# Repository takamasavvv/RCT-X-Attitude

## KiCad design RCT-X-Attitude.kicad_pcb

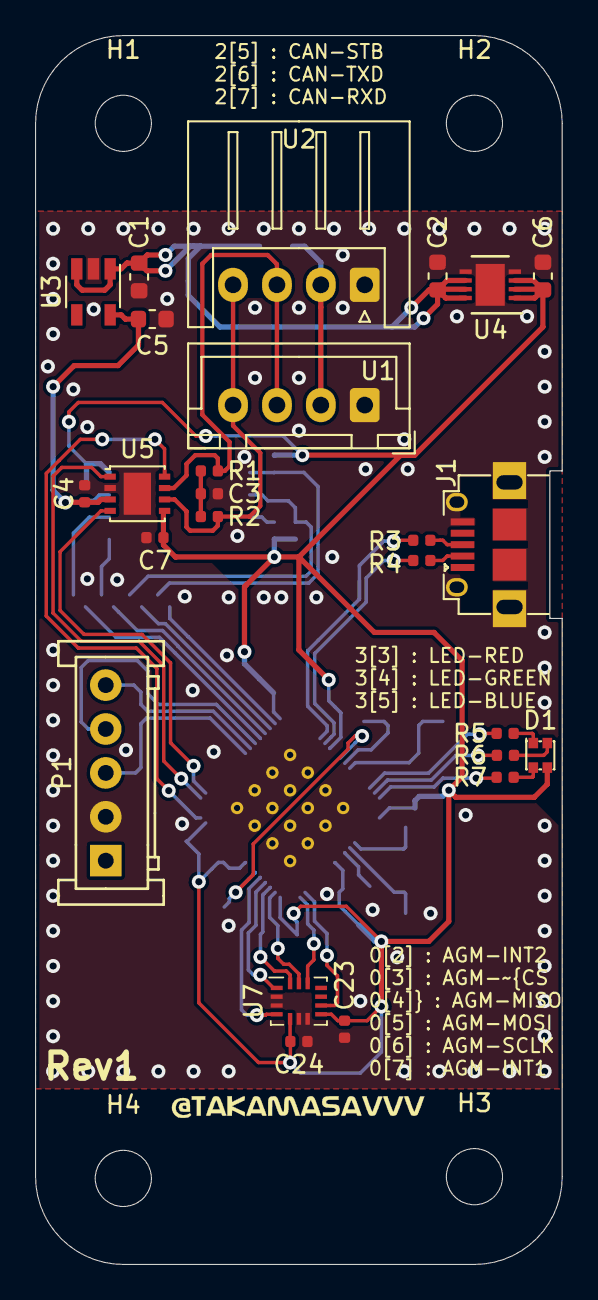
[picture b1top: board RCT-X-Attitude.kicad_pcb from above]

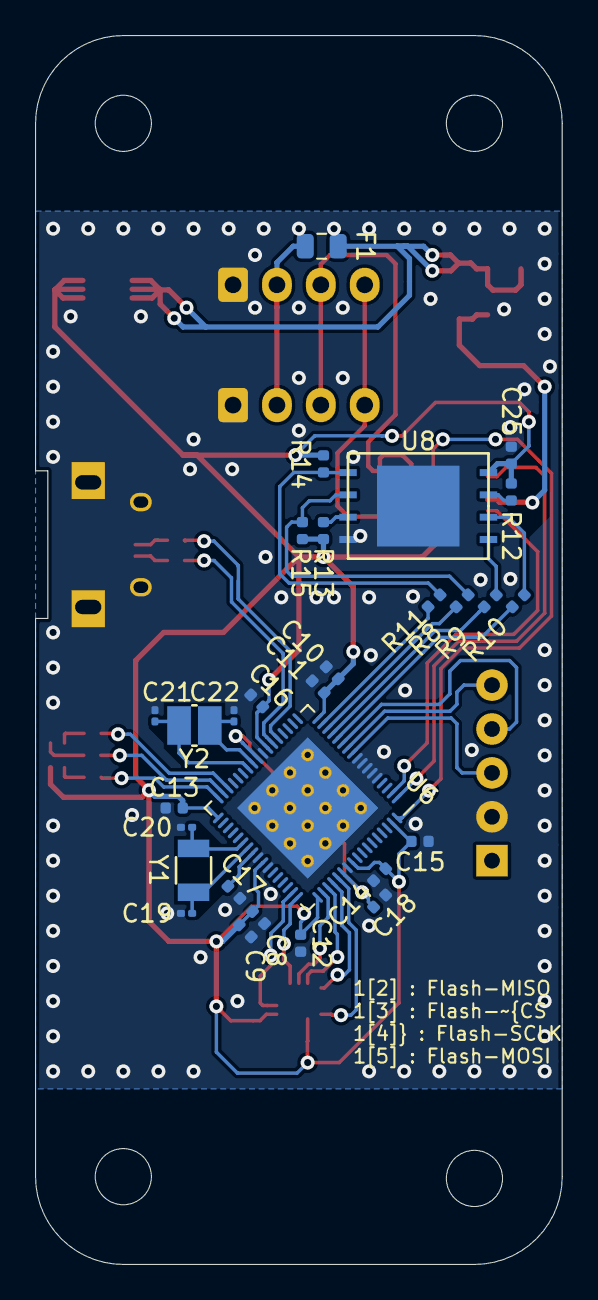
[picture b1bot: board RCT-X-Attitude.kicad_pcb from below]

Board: 2 copper layers, 30.0 x 70.0 mm, 58 parts (29 on the bottom side), 46 nets.

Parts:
C1, C2, C5, C6: 10uF; C_0603_1608Metric
C3: 4.7nF; C_0402_1005Metric
C4, C7, C8, C9, C10, C11, C12, C13, C15, C24, C25: 0.1uF; C_0402_1005Metric
C14, C16, C17, C18, C23: 1uF; C_0402_1005Metric
C19, C20, C21, C22: 9pF; C_0201_0603Metric
D1: LED_RGBA; LED_LiteOn_LTST-C19HE1WT
F1: Polyfuse; Fuse_0805_2012Metric
H1, H2, H3, H4: MountingHole; MountingHole_3.2mm_M3
J1: USB_B_Micro; Hirose_ZX_ZX62D-B-5P8
P1: KRC_Conn_SWD; JST_JQ_05JQ-BT_1x05_P2.5mm_Vertical
R1, R2: 56Ω; R_0402_1005Metric
R3, R4, R8, R9, R10, R11: 22Ω; R_0402_1005Metric
R5: 1.5kΩ; R_0402_1005Metric
R6, R7: 820Ω; R_0402_1005Metric
R12, R13, R14, R15: 4.7kΩ; R_0402_1005Metric
U1: KRC_Conn_CAN; JST_XH_B4B-XH-A_1x04_P2.50mm_Vertical
U2: KRC_Conn_CAN; JST_XH_S4B-XH-A_1x04_P2.50mm_Horizontal
U3: LT1761-5; TSOT-23-5
U4: LT1965xDD-3.3; DFN-8-1EP_3x3mm_P0.5mm_EP1.66x2.38mm
U5: NCV7342; DFN-8-1EP_3x3mm_P0.65mm_EP1.55x2.4mm
U6: CY8C58xxLTI-LPxxx; Cypress_QFN-68_EP_8x8_Pitch0.4mm
U7: BMX160; Bosch_LGA-14_3x2.5mm_P0.5mm
U8: W25N01GVxxIG-IT; WSON-8_8x6mm_P1.27mm
Y1: Crystal_kHz; Crystal_SeikoEpson_FC-135
Y2: Crystal_MHz; Crystal_Murata_XRCHA

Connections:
+3V3: C6.1, C7.1, C8.2, C9.2, C10.2, C11.2, C12.2, C13.2, C14.1, C15.2, C16.1, C23.2, C24.1, C25.2, D1.4, R12.2, R13.2, R14.2, R15.2, U4.1, U4.2, U4.3, U5.5, U6.17, U6.24, U6.35, U6.44, U6.52, U6.59, U6.67, U7.5, U7.8, U8.8
+5V: C4.1, C5.1, U3.5, U5.3
/AGM-INT1: U6.56, U7.4
/AGM-INT2: U6.50, U7.9
/AGM-MISO: U6.53, U7.13
/AGM-MOSI: U6.54, U7.14
/AGM-SCLK: U6.55, U7.1
/AGM-~CS: U6.51, U7.12
/CAN-RXD: U5.4, U6.2
/CAN-STB: U5.8, U6.68
/CAN-TXD: U5.1, U6.1
/Flash-MISO: R10.2, U6.13
/Flash-MOSI: R11.2, U6.16
/Flash-SCLK: R8.2, U6.15
/Flash-~CS: R9.2, U6.14
GND: C1.2, C2.2, C3.2, C4.2, C5.2, C6.2, C7.2, C8.1, C9.1, C10.1, C11.1, C12.1, C13.1, C14.2, C15.1, C16.2, C17.2, C18.2, C19.1, C20.1, C21.1, C22.1, C23.1, C24.2, C25.1, J1.5, P1.2, U1.1, U2.1, U3.2, U4.4, U4.5, U4.9, U5.2, U5.9, U6.5, U6.6, U6.7, U6.8, U6.9, U6.25, U6.43, U6.45, U6.58, U6.69, U7.2, U7.3, U7.6, U7.7, U8.4, U8.9
unnamed: C1.1, C2.1, F1.1, U3.1, U3.3, U4.6, U4.7, U4.8
unnamed: C3.1, R1.1, R2.2
unnamed: C17.1, U6.42
unnamed: C18.1, U6.26, U6.57
unnamed: C19.2, U6.41, Y1.1
unnamed: C20.2, U6.40, Y1.2
unnamed: C21.2, U6.28, Y2.1
unnamed: C22.2, U6.27, Y2.2
unnamed: D1.1, R5.2
unnamed: D1.2, R6.2
unnamed: D1.3, R7.2
unnamed: F1.2, U1.2, U2.2
unnamed: J1.2, R4.1
unnamed: J1.3, R3.1
unnamed: P1.3, U6.10
unnamed: P1.4, U6.12
unnamed: P1.5, U6.11
unnamed: R1.2, U1.3, U2.3, U5.7
unnamed: R2.1, U1.4, U2.4, U5.6
unnamed: R3.2, U6.22
unnamed: R4.2, U6.23
unnamed: R5.1, U6.32
unnamed: R6.1, U6.33
unnamed: R7.1, U6.34
unnamed: R9.1, U8.5
unnamed: R10.1, U8.6
unnamed: R11.1, R14.1, U8.1
unnamed: R12.1, U8.7
unnamed: R13.1, U8.3
unnamed: R8.1, R15.1, U8.2

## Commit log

2019-10-10 completed Rev1
